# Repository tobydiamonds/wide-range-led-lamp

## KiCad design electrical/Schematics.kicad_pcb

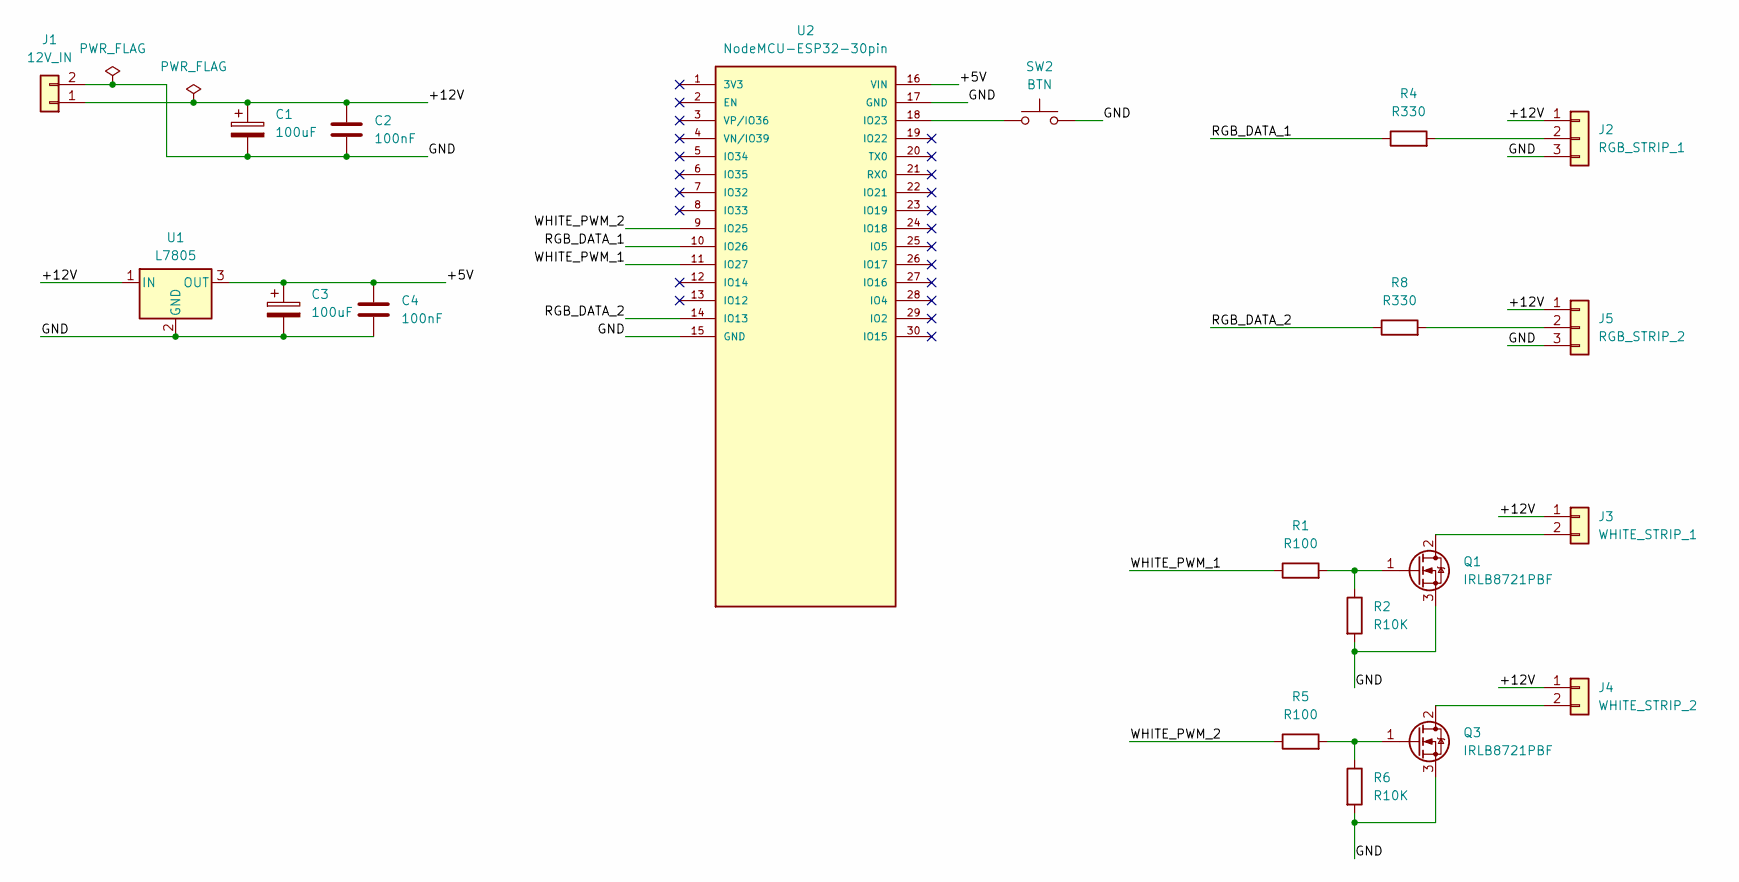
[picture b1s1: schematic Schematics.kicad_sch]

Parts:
C1, C3: 100uF; CP_Radial_D6.3mm_P2.50mm
C2, C4: 100nF; C_Disc_D5.0mm_W2.5mm_P5.00mm
J1: 12V_IN; TerminalBlock_Xinya_XY308-2.54-2P_1x02_P2.54mm_Horizontal
J2: RGB_STRIP_1; TerminalBlock_Xinya_XY308-2.54-3P_1x03_P2.54mm_Horizontal
J3: WHITE_STRIP_1; TerminalBlock_Xinya_XY308-2.54-2P_1x02_P2.54mm_Horizontal
J4: WHITE_STRIP_2; TerminalBlock_Xinya_XY308-2.54-2P_1x02_P2.54mm_Horizontal
J5: RGB_STRIP_2; TerminalBlock_Xinya_XY308-2.54-3P_1x03_P2.54mm_Horizontal
Q1, Q3: IRLB8721PBF; TO-220-3_Vertical
R1, R5: R100; R_Axial_DIN0207_L6.3mm_D2.5mm_P10.16mm_Horizontal
R2, R6: R10K; R_Axial_DIN0207_L6.3mm_D2.5mm_P10.16mm_Horizontal
R4, R8: R330; R_Axial_DIN0207_L6.3mm_D2.5mm_P10.16mm_Horizontal
SW2: BTN; SW_PUSH_6mm
U1: L7805; TO-220-3_Vertical
U2: NodeMCU-ESP32-30pin

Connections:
/+5V: C3.1, C4.1, U1.3 (OUT), U2.16 (VIN)
/+12V: C1.1, C2.1, J1.1, J2.1, J3.1, J4.1, J5.1, U1.1 (IN)
/GND: C1.2, C2.2, C3.2, C4.2, J1.2, J2.3, J5.3, Q1.3 (S), Q3.3 (S), R2.2, R6.2, SW2.2, U1.2 (GND), U2.15 (GND), U2.17 (GND)
/RGB_DATA_1: R4.1, U2.10 (IO26)
/RGB_DATA_2: R8.1, U2.14 (IO13)
/WHITE_PWM_1: R1.1, U2.11 (IO27)
/WHITE_PWM_2: R5.1, U2.9 (IO25)
unnamed: J2.2, R4.2
unnamed: J3.2, Q1.2 (D)
unnamed: J4.2, Q3.2 (D)
unnamed: J5.2, R8.2
unnamed: Q1.1 (G), R1.2, R2.1
unnamed: Q3.1 (G), R5.2, R6.1
unnamed: SW2.1, U2.18 (IO23)

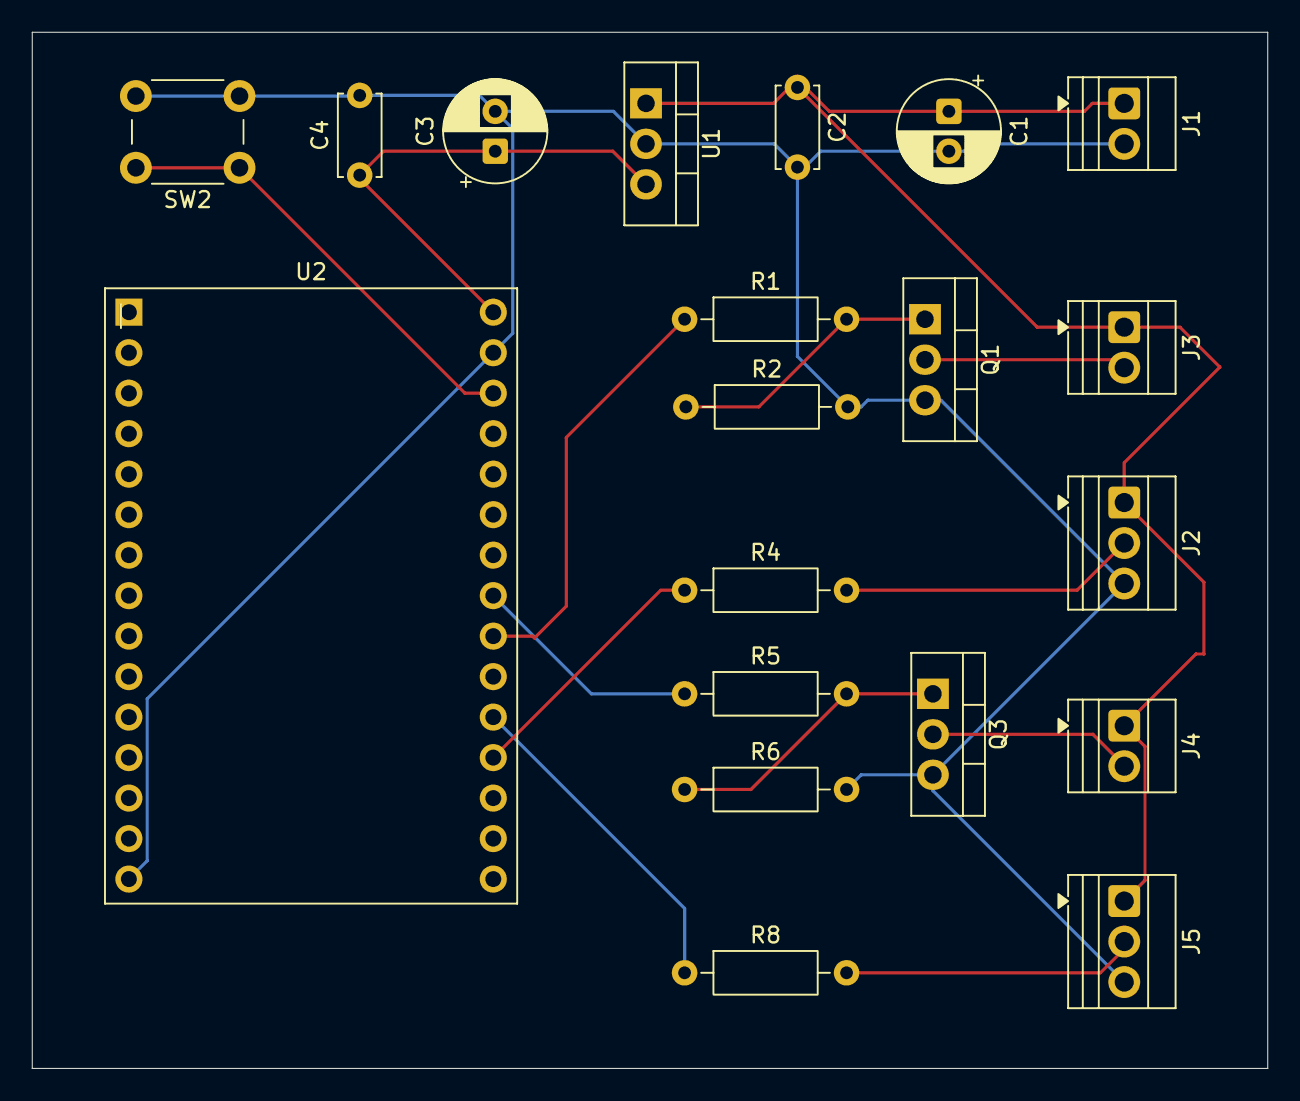
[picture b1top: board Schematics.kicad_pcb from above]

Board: 2 copper layers, 77.5 x 65.0 mm, 20 parts (0 on the bottom side), 14 nets.

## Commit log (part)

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2026-05-27 changed design to fit the ordered esp module
2026-05-29 changes according to actual build
